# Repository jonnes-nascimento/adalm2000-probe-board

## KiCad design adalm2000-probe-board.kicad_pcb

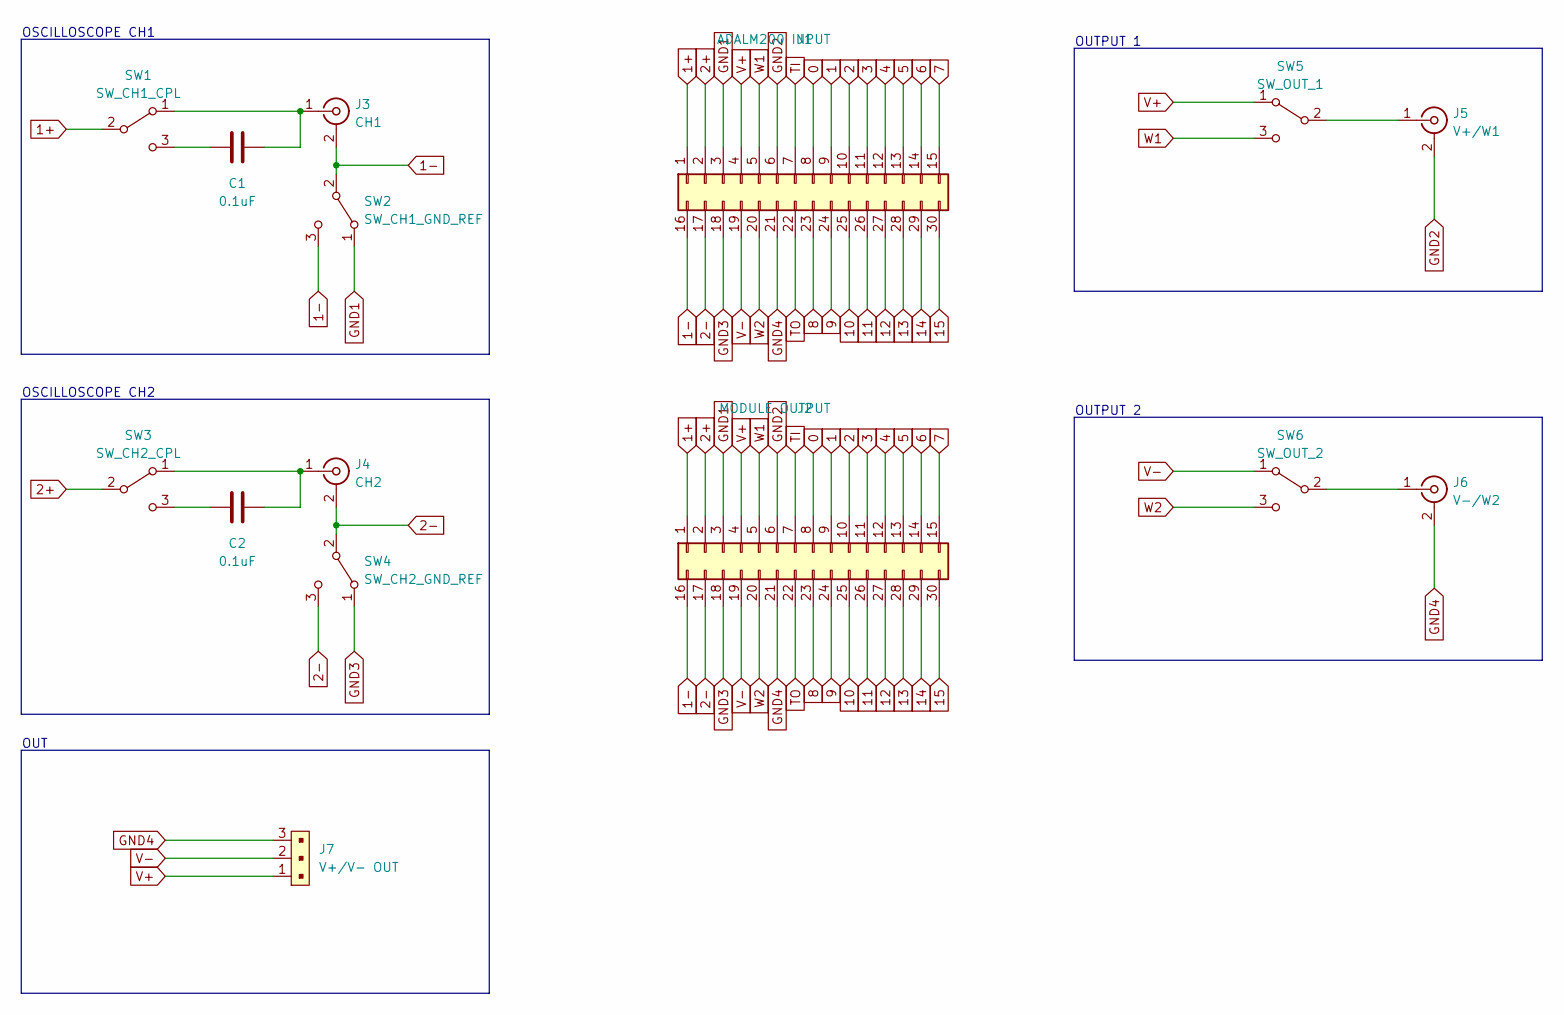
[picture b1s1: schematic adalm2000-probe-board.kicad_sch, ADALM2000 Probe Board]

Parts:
C1, C2: 0.1uF; C_0805_2012Metric
J1: ADALM200 INPUT; PinSocket_2x15_P2.54mm_Horizontal
J2: MODULE OUTPUT; IDC-Header_2x15_P2.54mm_Horizontal - Pin 1 on left from fro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
J3: CH1; bnc_90_1-1337543-0
J4: CH2; bnc_90_1-1337543-0
J5: V+/W1; bnc_90_1-1337543-0
J6: V-/W2; bnc_90_1-1337543-0
J7: V+/V- OUT; PinHeader_1x3_P2.54_Drill1.1mm; MPN 61300311121; Digi-Key_PN 732-5316-ND
SW1: SW_CH1_CPL; SS12D00G3
SW2: SW_CH1_GND_REF; SS12D00G3
SW3: SW_CH2_CPL; SS12D00G3
SW4: SW_CH2_GND_REF; SS12D00G3
SW5: SW_OUT_1; SS12D00G3
SW6: SW_OUT_2; SS12D00G3

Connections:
0: J1.8, J2.8
1: J1.9, J2.9
1+: J1.1, J2.1, SW1.2 (B)
1-: J1.16, J2.16, J3.2 (Ext), SW2.2 (B), SW2.3 (C)
2: J1.10, J2.10
2+: J1.2, J2.2, SW3.2 (B)
2-: J1.17, J2.17, J4.2 (Ext), SW4.2 (B), SW4.3 (C)
3: J1.11 (Pin_1), J2.11
4: J1.12, J2.12
5: J1.13, J2.13
6: J1.14, J2.14
7: J1.15, J2.15
8: J1.23, J2.23
9: J1.24, J2.24
10: J1.25, J2.25
11: J1.26, J2.26
12: J1.27, J2.27
13: J1.28, J2.28
14: J1.29, J2.29
15: J1.30, J2.30
GND1: J1.3, J2.3, SW2.1 (A)
GND2: J1.6, J2.6, J5.2 (Ext)
GND3: J1.18, J2.18, SW4.1 (A)
GND4: J1.21, J2.21, J6.2 (Ext), J7.3
unnamed: C1.1, SW1.3 (C)
unnamed: C1.2, J3.1 (In), SW1.1 (A)
unnamed: C2.1, SW3.3 (C)
unnamed: C2.2, J4.1 (In), SW3.1 (A)
unnamed: J5.1 (In), SW5.2 (B)
unnamed: J6.1 (In), SW6.2 (B)
TI: J1.7, J2.7
TO: J1.22, J2.22
V+: J1.4, J2.4, J7.1, SW5.1 (A)
V-: J1.19, J2.19, J7.2, SW6.1 (A)
W1: J1.5, J2.5, SW5.3 (C)
W2: J1.20, J2.20, SW6.3 (C)

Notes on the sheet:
OUTPUT 2
OUT
OSCILLOSCOPE CH2
OSCILLOSCOPE CH1
OUTPUT 1

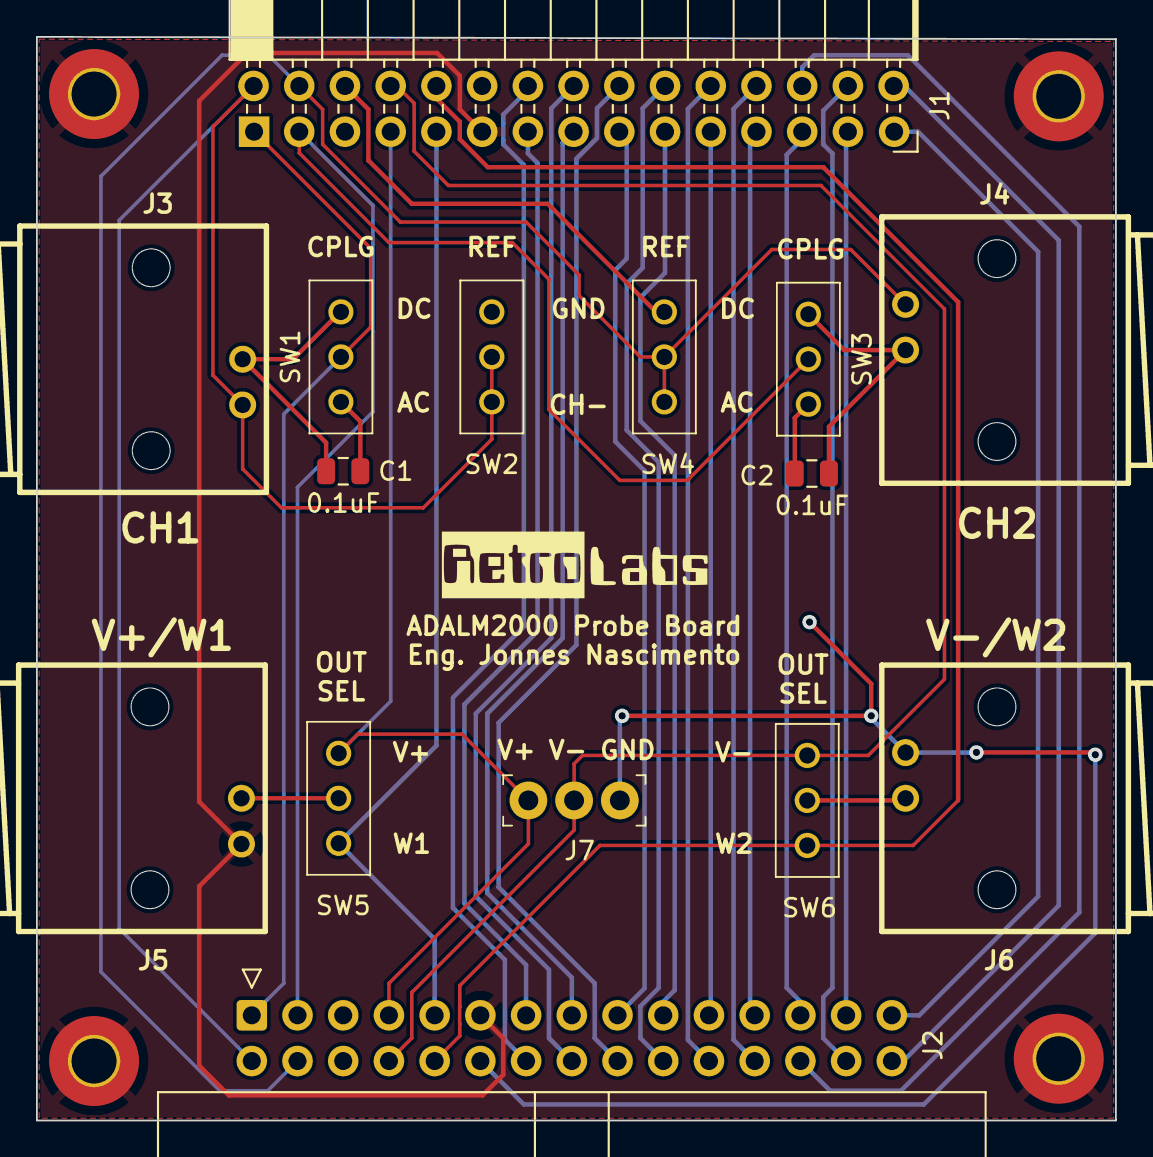
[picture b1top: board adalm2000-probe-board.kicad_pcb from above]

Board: 4 copper layers, 59.9 x 60.2 mm, 15 parts (0 on the bottom side), 36 nets.

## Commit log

2022-11-30 Initial PCB design
2022-12-01 Adding images and configuring board layers
2022-12-02 Board initial routing
